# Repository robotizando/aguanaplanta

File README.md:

# aguanaplanta

Repositório do sensor para plantas, referente à oficina de eletrônica para Iniciantes

## Bibliografia

https://www.newtoncbraga.com.br/index.php/mini-projetos/166-ativadores-e-controladores/9107-sensor-de-umidade-min504.html

https://wiki.sj.ifsc.edu.br/wiki/images/1/11/ELA1_Amplificador.pdf

Oficina de eletrônica para inciantes - Água na Planta!

Você está aprendendo eletrônica e gosta de plantas? ou gosta de eletrônica e está aprendendo lidar com plantas? Esse projeto é para você!

Nesta Oficina você irá aprender como funcionam os amplificadores de sinal e vai aprender montar um circuito que lhe ajudará a saber se a sua plantinha está precisando de água ou não.

Oficina para 10 participantes, duração de duas horas.
Podemos fazer duas oficinas iguais, uma em um dia e outra no outro
Material e ferramentas fornecidos

Mini Biografia

Daniel Basconcello Filho é desenvolvedor de hardware e software e ativista das tecnologias livres. Conheça mais o seu trabalho em www.robotizando.com.br

Confira na pasta de imagens neste repositório, em breve teremos o material completo da oficina disponibilizado aqui

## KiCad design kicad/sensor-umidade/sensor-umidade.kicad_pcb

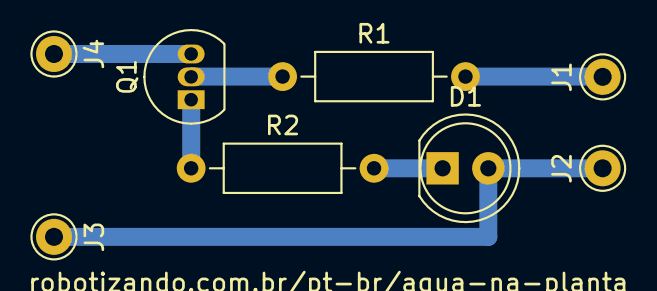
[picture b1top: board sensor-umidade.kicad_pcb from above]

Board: 2 copper layers, 8 parts (0 on the bottom side), 6 nets.

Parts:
D1: LED; LED_D5.0mm
J1, J2, J3, J4: Conn_01x01_MountingPin; Pin_D1.0mm_L10.0mm
Q1: BC549; TO-92_Inline
R1, R2: R; R_Axial_DIN0207_L6.3mm_D2.5mm_P10.16mm_Horizontal

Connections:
+3V0: D1.2, J2.1, J3.1
GND: J4.1, Q1.3
unnamed: D1.1, R2.2
unnamed: J1.1, R1.2
unnamed: Q1.1, R2.1
unnamed: Q1.2, R1.1

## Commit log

2021-09-14 9V batttery clip 3d object, draft for kicad files.
2021-09-28 kicad sensor PCB done
